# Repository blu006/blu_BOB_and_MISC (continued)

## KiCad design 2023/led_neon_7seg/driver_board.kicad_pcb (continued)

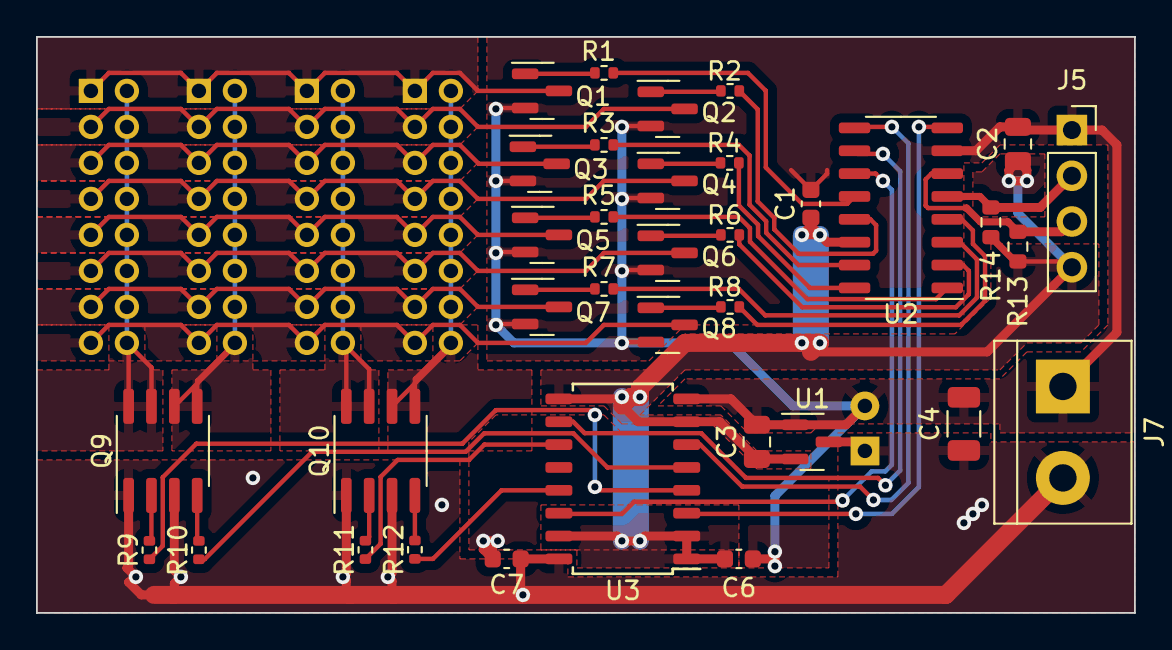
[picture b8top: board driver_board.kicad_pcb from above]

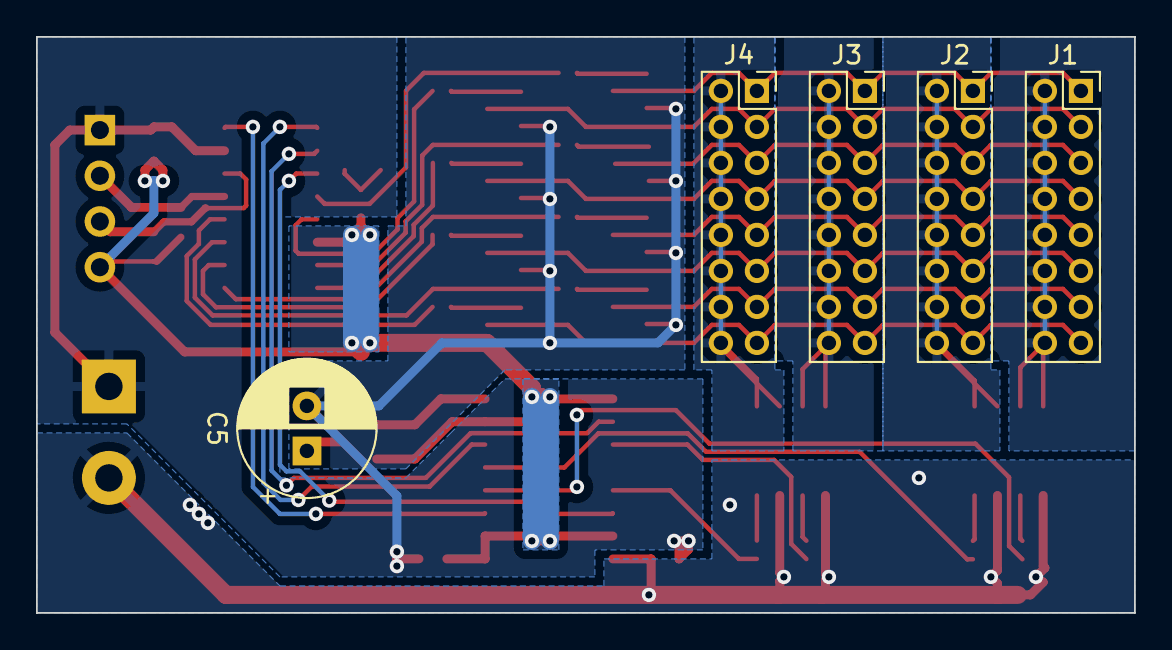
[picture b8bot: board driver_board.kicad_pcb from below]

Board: 2 copper layers, 61.0 x 32.0 mm, 40 parts (5 on the bottom side), 45 nets.
